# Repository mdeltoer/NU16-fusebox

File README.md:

# NU16 Fusebox
Part of the 2020 rebuild of NU16, the fusebox is made from a PCB rather than having a mess of wires everywhere.

## Schematic

### LEDs
These green LEDs are just indicators of whether the fuse is working or not.

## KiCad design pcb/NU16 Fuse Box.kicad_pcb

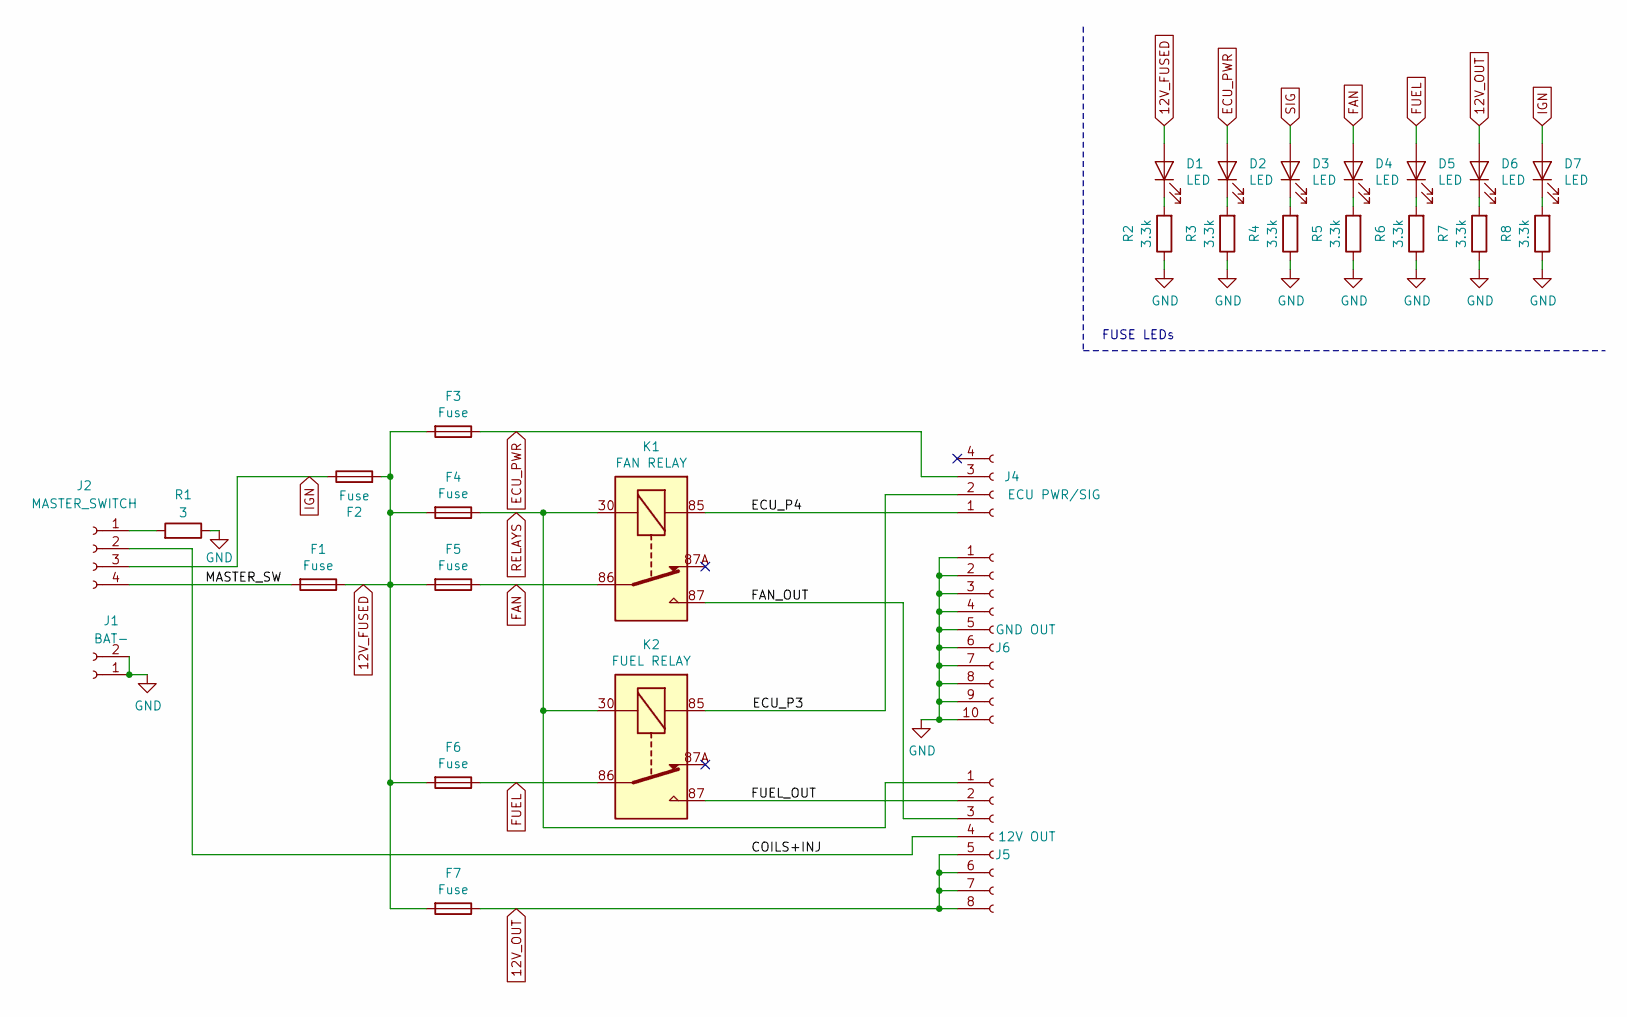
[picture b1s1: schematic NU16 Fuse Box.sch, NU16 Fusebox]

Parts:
D1, D2, D3, D4, D5, D6, D7: LED; LED_0805_2012Metric
F1: Fuse; Fuse-BladeLarge-THT
F2, F3, F4, F5, F6, F7: Fuse; Fuse-BladeMini-THT
J1: BAT-; Molex_Mini-Fit_Sr_42819-22XX_1x02_P10.00mm_Vertical
J2: MASTER_SWITCH; Molex_Mini-Fit_Sr_42819-42XX_1x04_P10.00mm_Vertical
J4: ECU PWR/SIG; Molex-Mini-Fit-Jr-4-pin-P4.2mm-RowP4.2mm
J5: 12V OUT; Molex-Mini-Fit-Jr-8-pin-P4.2mm-RowP4.2mm
J6: GND OUT; Molex-Mini-Fit-Jr-10-pin-P4.2mm-RowP4.2mm
K1: FAN RELAY; TE_VCF4-1000
K2: FUEL RELAY; TE_VCF4-1000
R1: 3; R_Axial_Power_L50.0mm_W9.6mm_P55.00mm
R2, R3, R4, R5, R6, R7, R8: 3.3k; R_1206_3216Metric

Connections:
12V_FUSED: D1.2 (A), F1.1, F2.2, F3.2, F4.2, F5.2, F6.2, F7.2
12V_OUT: D6.2 (A), F7.1, J5.5, J5.6, J5.7, J5.8
/COILS+INJ: J2.2, J5.4
/ECU_P3: J4.2, K2.85
/ECU_P4: J4.1, K1.85
/FAN_OUT: J5.3, K1.87
/FUEL_OUT: J5.2, K2.87
/MASTER_SW: F1.2, J2.4
ECU_PWR: D2.2 (A), F3.1, J4.3
FAN: D4.2 (A), F5.1, K1.86
FUEL: D5.2 (A), F6.1, K2.86
GND: J1.1, J1.2, J6.1, J6.2, J6.3, J6.4, J6.5, J6.6, J6.7, J6.8, J6.9, J6.10, R1.1, R2.1, R3.1, R4.1, R5.1, R6.1, R7.1, R8.1
IGN: D7.2 (A), F2.1, J2.3
unnamed: D1.1 (K), R2.2
unnamed: D2.1 (K), R3.2
unnamed: D3.1 (K), R4.2
unnamed: D4.1 (K), R5.2
unnamed: D5.1 (K), R6.2
unnamed: D6.1 (K), R7.2
unnamed: D7.1 (K), R8.2
unnamed: J2.1, R1.2

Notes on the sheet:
FUSE LEDs

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
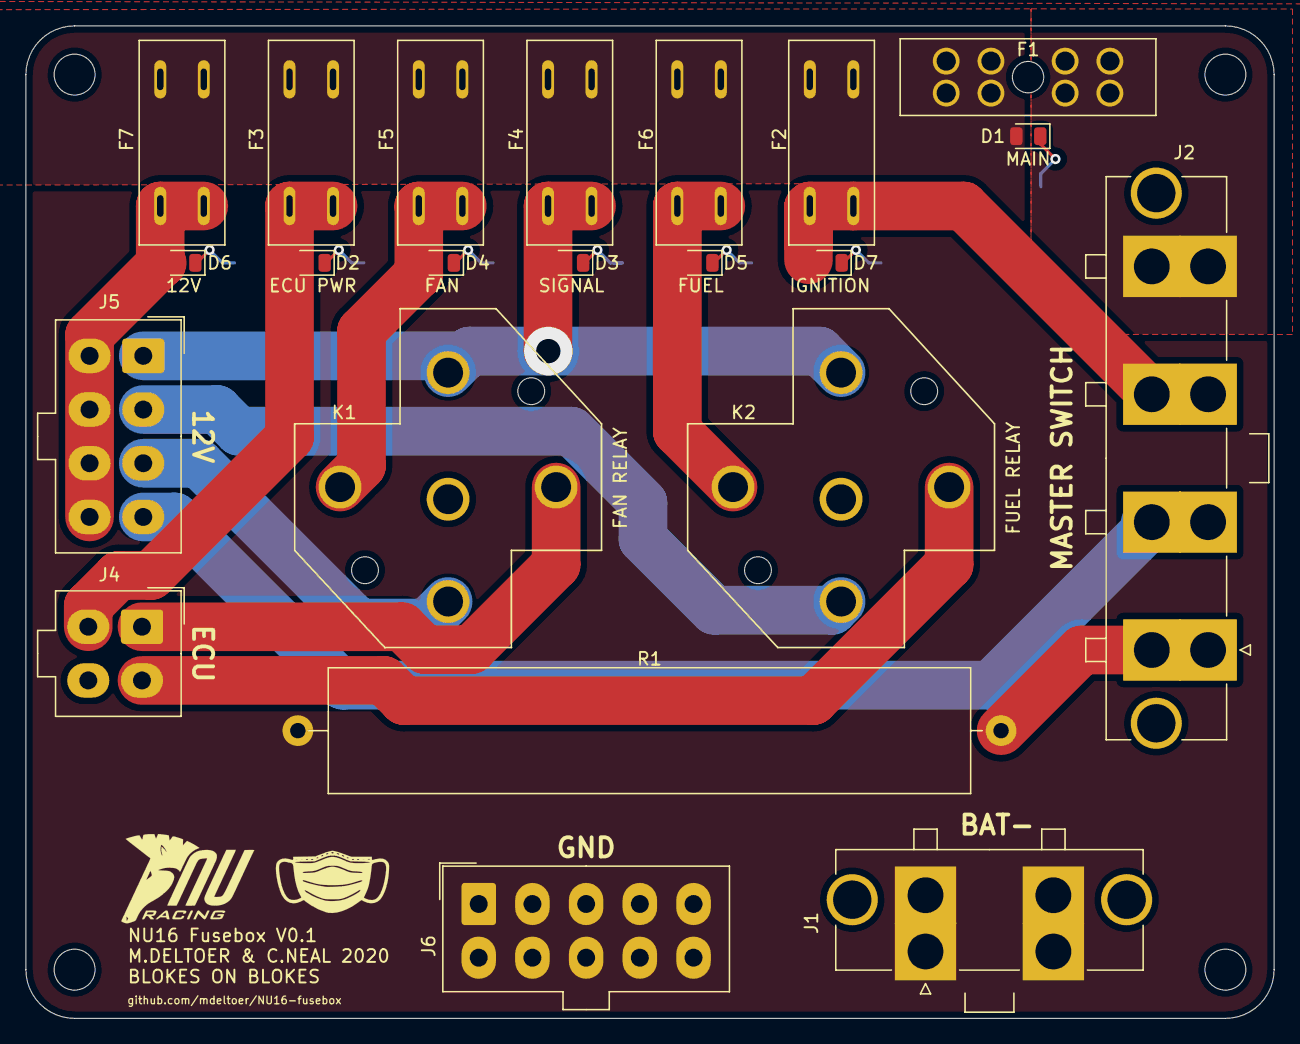
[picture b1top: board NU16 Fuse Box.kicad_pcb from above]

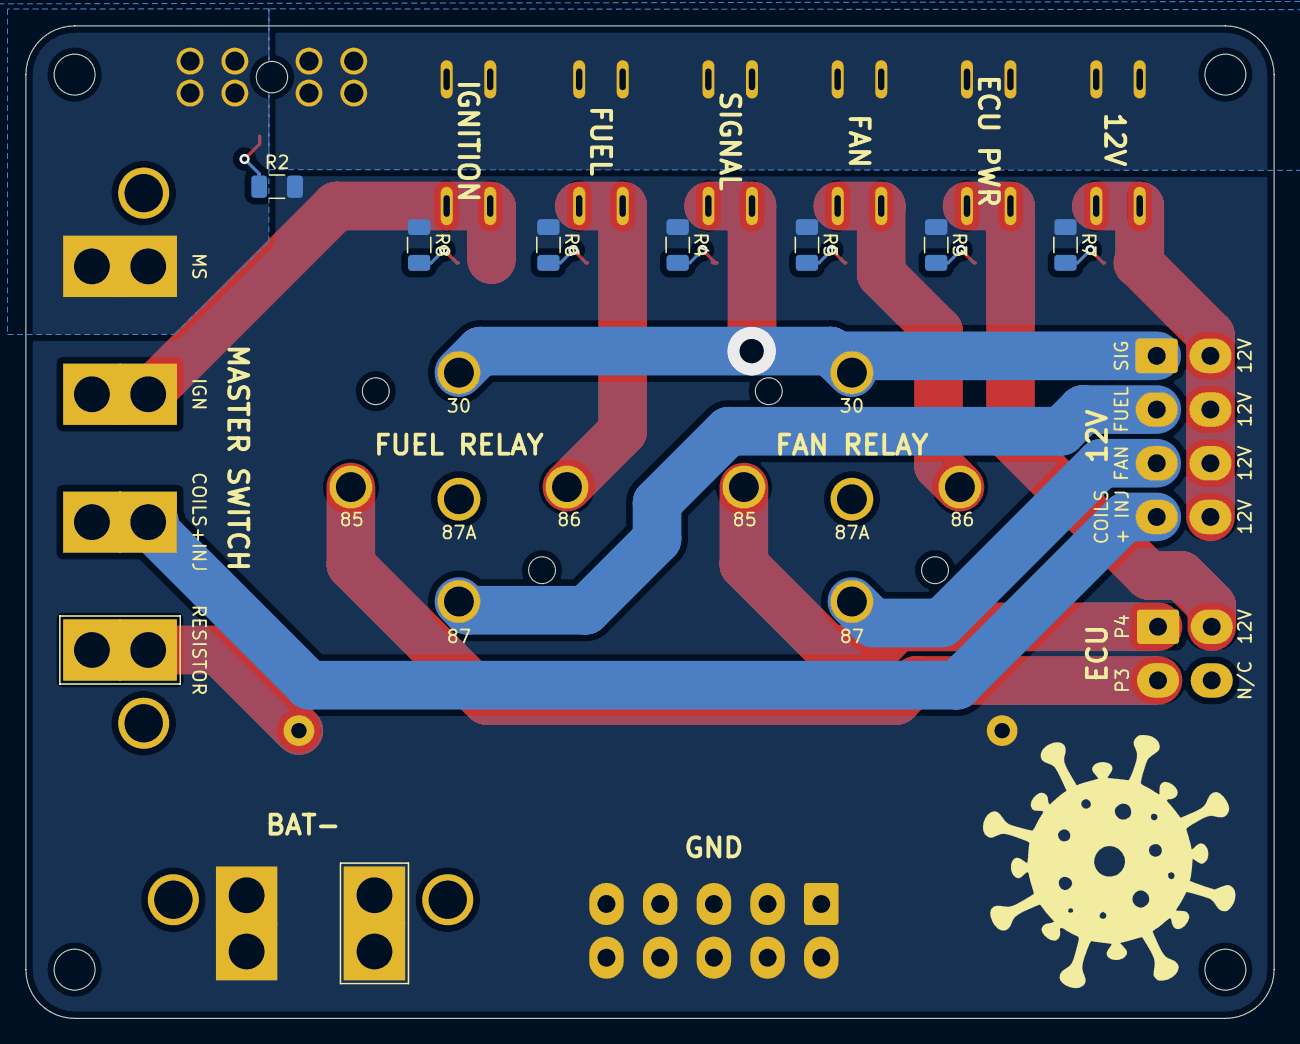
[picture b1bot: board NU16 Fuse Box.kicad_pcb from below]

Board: 2 copper layers, 97.6 x 77.6 mm, 29 parts (7 on the bottom side), 22 nets.

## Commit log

2020-10-07 Initial commit.
2020-10-07 :hammer: Changed copper fill to be more aesthetic.
